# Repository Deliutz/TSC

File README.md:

# InkTime Smartwatch Project

Proiect hardware pentru realizarea unui smartwatch open-source low-cost, bazat pe microcontrollerul **Nordic nRF52840**, proiectat în **Autodesk Fusion 360 Electronics**.

---

# Diagrama bloc

```text
Baterie LiPo
    |
    v
+------------------+
|   BQ25180YBGR    |
| Charger / PMIC   |
+------------------+
    |
    v
+------------------+
|    RT6160AWSC    |
| Buck-Boost 3.3V  |
+------------------+
    |
    v
+------------------+
|    nRF52840      |
|   MCU + BLE      |
+------------------+
   |      |      |      |      |
   |      |      |      |      |
   |      |      |      |      +-------------------+
   |      |      |      |                          |
   |      |      |      v                          v
   |      |      |  +---------+              +-----------+
   |      |      |  | Buttons |              | TC2030    |
   |      |      |  | 3x GPIO |              | SWD Debug |
   |      |      |  +---------+              +-----------+
   |      |      |
   |      |      +-------------------+
   |      |                          |
   |      v                          v
   |  +-----------+            +------------+
   |  | DRV2605   |----------->| Vibra motor|
   |  | Haptic IC |            +------------+
   |  +-----------+
   |
   +---------------------+
   |                     |
   v                     v
+---------+         +-----------+
| BMA421  |         | MAX17048  |
| IMU     |         | Fuel Gauge|
+---------+         +-----------+
   ^                     ^
   |                     |
   +--------- I2C -------+

```

---

# Bill of Materials (BOM)

| Componenta | Cod | Rol | Interfata |
|---|---|---|---|
| NRF52840_QF | U1 | Microcontroller principal + BLE | SPI / I2C / GPIO |
| BQ25180YBGR | IC1 | Incarcare baterie LiPo / power management | Power / I2C |
| RT6160AWSC | IC9 | Convertor buck-boost 3.3V | Power |
| BMA421 | IC3 | Accelerometru / IMU | I2C |
| DRV2605YZFR | IC2 | Driver feedback haptic | I2C / GPIO |
| MAX17048G+T10 | U3 | Fuel gauge baterie | I2C |
| KH-TYPE-C-16P | J4 | Conector USB-C | USB |
| USBLC6-2SC6Y | D3 | Protectie ESD USB | USB |
| 503480-2400 | J2 | Conector display e-paper | SPI |
| 2450AT18B100E | ANT1 | Antena 2.4 GHz BLE | RF |
| TC2030-IDC | J1 | Conector debugging SWD | SWD |
| SW_UP / SW_ENT / SW_DN | SW_UP, SW_ENT, SW_DN | Input utilizator | GPIO |
| X1 | X1 | Cristal de mare frecventa pentru nRF52840 | Clock |
| X2 32.768kHz | X2 | Cristal RTC / low power clock | Clock |
| SI1308EDL-T1-GE3 | Q3 | MOSFET pentru comutare alimentare | Power / GPIO |
| Q1 | Q1 | MOSFET pentru power switching | Power |
| FTC252012SR47MBCA | L7 | Inductor pentru regulatorul de tensiune | Power |
| MBR0530 | D2, D4, D5 | Diode Schottky pentru protectie / redresare | Power |
| TP_* | TP_3.3V, TP_3V3, TP_BAT_GND, TP_GND, TP_ON, TP_OP, TP_RESET, TP_SCL, TP_SDA, TP_SWDCLK, TP_SWDIO, TP_SWO, TP_VBAT, TP_VREG | Test pads pentru validare si debugging | Test / Debug |

---

# Funcționalitate hardware
Designul este construit în jurul microcontrollerului **nRF52840**, responsabil de:
- comunicația Bluetooth Low Energy;
- citirea senzorilor;
- controlul display-ului e-paper;
- gestionarea butoanelor;
- controlul feedback-ului haptic;
- monitorizarea bateriei.

## Alimentare
- **BQ25180** gestionează încărcarea bateriei LiPo;
- **RT6160** generează tensiunea stabilă de **3.3V**;
- **MAX17048** monitorizează nivelul bateriei.

## Senzori și periferice
- **BMA423** este conectat prin **I2C**;
- display-ul e-paper este conectat prin conectorul FPC;
- **DRV2605** comandă motorul de vibrații;
- USB-C este folosit pentru alimentare și debugging.

---

# Utilizarea pinilor nRF52840
## Magistrală I2C
- SDA → IMU + Fuel Gauge
- SCL → IMU + Fuel Gauge

## SWD
- SWDIO
- SWDCLK
- SWO
- RESET

## GPIO
- Buton UP
- Buton ENTER
- Buton DOWN
- semnale control display
- semnal driver haptic

## SPI
- semnale rutate către conectorul display-ului e-paper

---

# Proces de proiectare

## 1. Schematic
În prima etapă am realizat schema electrică pornind de la modelul oferit pe OCW și folosind exclusiv biblioteca pusă la dispoziție.

Am implementat blocurile:
- LiPo Charger
- DC/DC
- IMU
- SWD
- E-Paper Driver
- Fuel Gauge
- Haptic Driver
- Buttons
- USB-C + ESD

În timpul realizării schemei:
- am modificat valorile componentelor pasive;
- am adăugat condensatoare de decuplare;
- am etichetat semnalele importante;
- am separat schematicul pe blocuri funcționale.

---

## 2. PCB Design
PCB-ul a fost realizat pe baza dimensiunilor mecanice recomandate.

Etapele principale:
- placement TOP pentru componentele critice;
- amplasarea componentelor pasive lângă pinii de alimentare;
- rutare pe mai multe straturi;
- plane dedicate de GND;
- păstrarea zonei antenei liberă;
- alinierea USB-C și a butoanelor cu carcasa.

La final am rulat DRC și am corectat erorile principale.

---

## 3. Model 3D
Modelul 3D include:
- PCB
- baterie
- display
- carcasă

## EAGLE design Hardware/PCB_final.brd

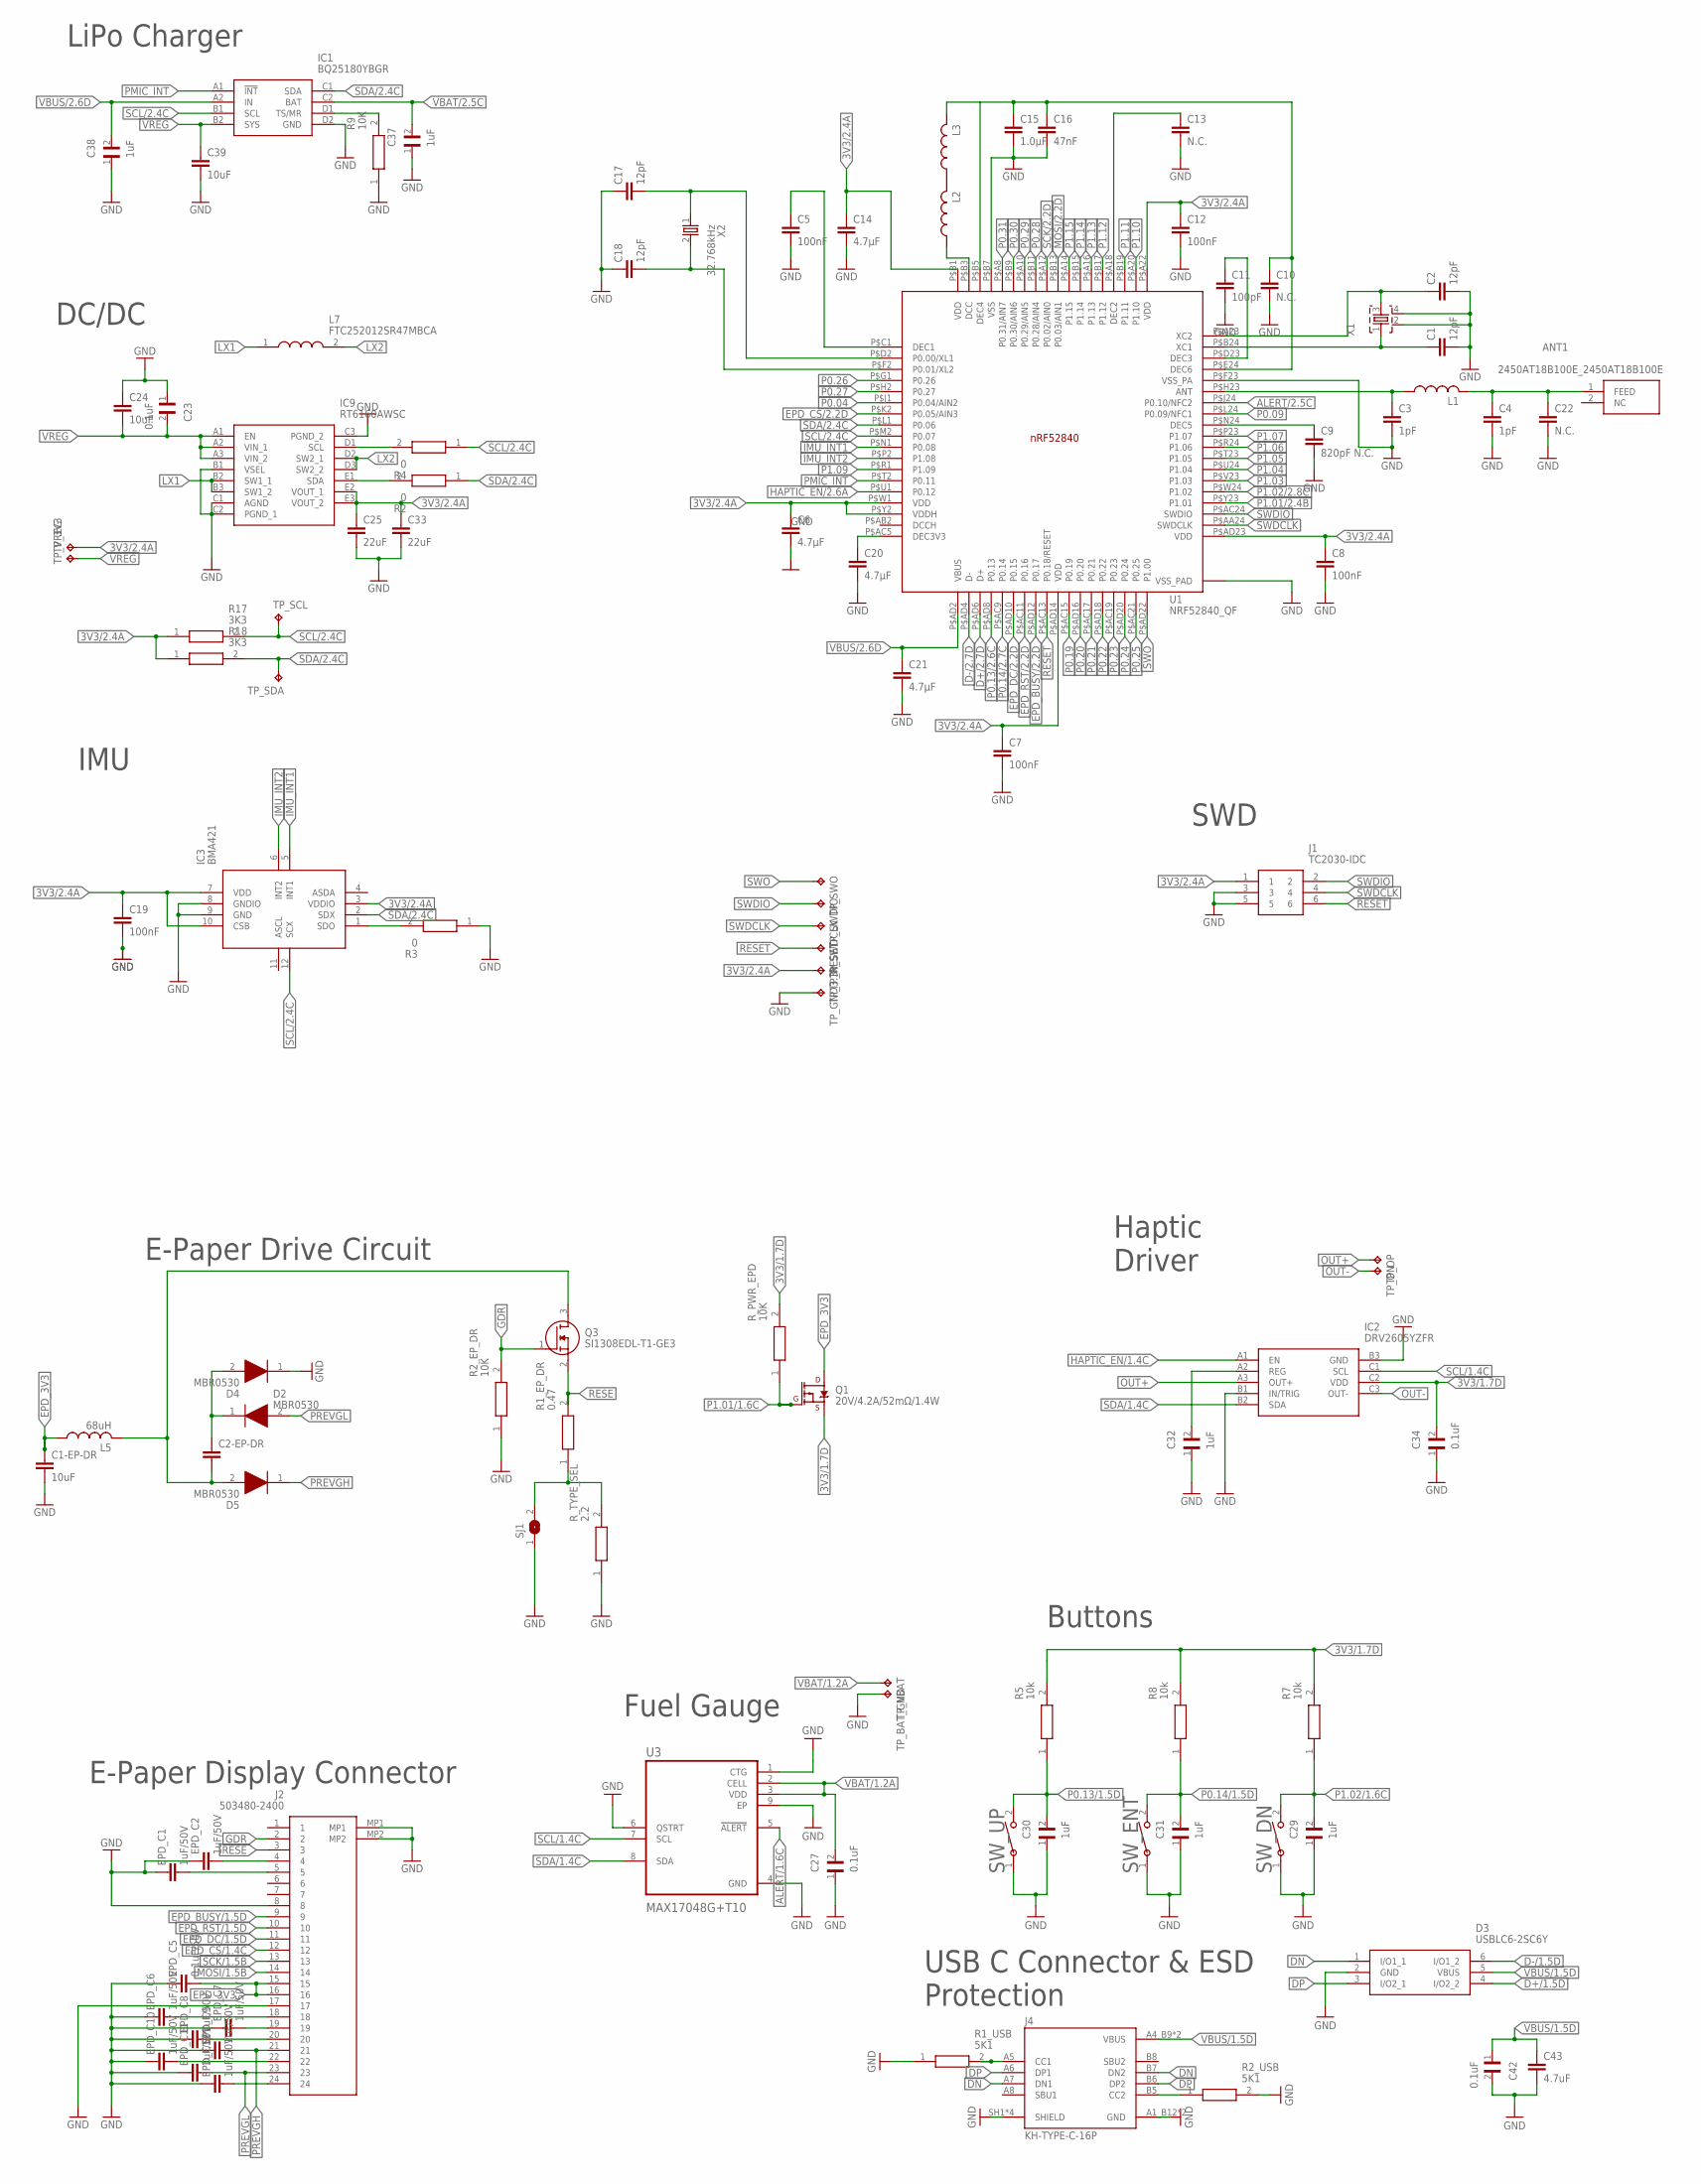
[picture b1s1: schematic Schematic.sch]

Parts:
ANT1: 2450AT18B100E_2450AT18B100E; 2450AT18B100E_ANTC3216X140N
C1, C2, C17, C18: 12pF; NORDIC_NRF_3_RESC0201_L
C1-EP-DR, C24, C39: 10uF; NORDIC_NRF_3_RESC0201_L
C2-EP-DR: NORDIC_NRF_3_CAPACITOR_0201_L; NORDIC_NRF_3_RESC0201_L
C3, C4: 1pF; NORDIC_NRF_3_RESC0201_L
C5, C7, C8, C12, C19: 100nF; NORDIC_NRF_3_RESC0201_L
C6: 4.7µF; NORDIC_NRF_3_RESC0201_L
C9: 820pF N.C.; NORDIC_NRF_3_RESC0201_L
C10, C13, C22: N.C.; NORDIC_NRF_3_RESC0201_L
C11: 100pF; NORDIC_NRF_3_RESC0201_L
C14, C20, C21: 4.7µF; ESP32_C6_LIBRARY_1_ESP32_WROVER_EAGLE-LTSPICE_C0402
C15: 1.0µF; NORDIC_NRF_3_RESC0201_L
C16: 47nF; NORDIC_NRF_3_RESC0201_L
C23, C34: 0.1uF; GRM011R60J152KE01L_2_CAPC0201X13N
C25, C33: 22uF; NORDIC_NRF_3_RESC0201_L
C27, C42: 0.1uF; GRM011R60J152KE01L_1_0201
C29, C30, C31: 1uF; GRM011R60J152KE01L_1_0201
C32, C37, C38: 1uF; GRM011R60J152KE01L_2_CAPC0201X13N
C43: 4.7uF; NORDIC_NRF_3_RESC0201_L
D2, D4, D5: MBR0530; ESP32_C6_LIBRARY_5_SOD3716X135N
D3: USBLC6-2SC6Y; ESP32_C6_LIBRARY_3_SOT95P280X145-6N
EPD_C1, EPD_C2, EPD_C6, EPD_C7, EPD_C8, EPD_C9, EPD_C10, EPD_C11, EPD_C12: 1uF/50V; PERFECT_0402_0402
EPD_C5: 0.1uF/50V; PERFECT_0402_0402
IC1: BQ25180YBGR; BQ25180YBGR_BGA8C40P2X4_100X155X50
IC2: DRV2605YZFR; DRV2605YZFR_BGA9C50P3X3_144X144X62
IC3: BMA421; BMA423_BMA423
IC9: RT6160AWSC; RT6160AWSC_BGA15C40P3X5_140X230X60
J1: TC2030-IDC; TC2030-IDC_TC2030IDC
J2: 503480-2400; 503480-2400_5034802400
J4: KH-TYPE-C-16P; KH-TYPE-C-16P_KINGHELM_KH-TYPE-C-16P
L1, L2, L3: NORDIC_NRF_2_INDUCTOR_0402_L; NORDIC_NRF_2_RESC0402_L
L5: 68uH; NORDIC_NRF_2_RESC0402_L
L7: FTC252012SR47MBCA; MLP2016SR47MT0S1_INDC2016X100N
Q1: 20V/4.2A/52mΩ/1.4W; ESP32_C6_LIBRARY_4_ESP32_C6_LIBRARY_4_ESP32_C6_LIBRARY_4_ES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
Q3: SI1308EDL-T1-GE3; ESP32_C6_LIBRARY_6_SOT65P210X110-3N
R1_EP_DR: 0.47; ERA-1AEB3401C_0201
R1_USB, R2_USB: 5K1; CPF0201D7K68C1_0201
R2, R4: 0; ERA-1AEB3401C_0201
R2_EP_DR, R9: 10K; ERA-1AEB3401C_0201
R3: 0; CPF0201D7K68C1_0201
R5, R7, R8: 10k; CPF0201D7K68C1_0201
R17, R18: 3K3; ERA-1AEB3401C_0201
R_PWR_EPD: 10K; ERA-1AEB3401C_0201
R_TYPE_SEL: 2.2; ERA-1AEB3401C_0201
SJ1: ESP32_C6_LIBRARY_7_JUMPER_SJ
SW_DN: 2025-10-22_07-23-44_LIBRARY_EVP-AKE31ASW_EVP-AKE3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; 2025-10-22_07-23-44_LIBRARY_SW_EVP-AKE31A_PAN
SW_ENT: 2025-10-22_07-23-44_LIBRARY_EVP-AKE31ASW_EVP-AKE3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; 2025-10-22_07-23-44_LIBRARY_SW_EVP-AKE31A_PAN
SW_UP: 2025-10-22_07-23-44_LIBRARY_EVP-AKE31ASW_EVP-AKE3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; 2025-10-22_07-23-44_LIBRARY_SW_EVP-AKE31A_PAN
TP_3.3V, TP_3V3: HECTOR_WATCH_1_TPTP20R; HECTOR_WATCH_1_TP20R
TP_BAT_GND: HECTOR_WATCH_1_TPTP20R; HECTOR_WATCH_1_TP20R
TP_GND: HECTOR_WATCH_1_TPTP20R; HECTOR_WATCH_1_TP20R
TP_ON: HECTOR_WATCH_1_TPTP20R; HECTOR_WATCH_1_TP20R
TP_OP: HECTOR_WATCH_1_TPTP20R; HECTOR_WATCH_1_TP20R
TP_RESET: HECTOR_WATCH_1_TPTP20R; HECTOR_WATCH_1_TP20R
TP_SCL: HECTOR_WATCH_1_TPTP20R; HECTOR_WATCH_1_TP20R
TP_SDA: HECTOR_WATCH_1_TPTP20R; HECTOR_WATCH_1_TP20R
TP_SWDCLK: HECTOR_WATCH_1_TPTP20R; HECTOR_WATCH_1_TP20R
TP_SWDIO: HECTOR_WATCH_1_TPTP20R; HECTOR_WATCH_1_TP20R
TP_SWO: HECTOR_WATCH_1_TPTP20R; HECTOR_WATCH_1_TP20R
TP_VBAT: HECTOR_WATCH_1_TPTP20R; HECTOR_WATCH_1_TP20R
TP_VREG: HECTOR_WATCH_1_TPTP20R; HECTOR_WATCH_1_TP20R
U1: NRF52840_QF; NORDIC_NRF_4_AQFN50P700X700X85_HS-74N
U3: MAX17048G+T10; ESP32_C6_LIBRARY_SON50P200X200X80-9N
X1: NORDIC_NRF_XTAL_32MHZ; NORDIC_NRF_BT-XTAL_2016_N
X2: 32.768kHz; NORDIC_NRF_1_XTAL_3215_N

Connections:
3V3/1.7D: C34.2, IC2.C2 (VDD), Q1.2 (S), R5.2, R7.2, R8.2, R_PWR_EPD.2
3V3/2.4A: C6.1, C7.1, C8.1, C12.1, C14.1, C19.1, C25.1, C33.1, IC3.3 (VDDIO), IC3.7 (VDD), IC3.10 (CSB), IC9.E2 (VOUT_1), IC9.E3 (VOUT_2), J1.1, R17.1, R18.1, TP_3.3V.TP, TP_3V3.TP, U1.P$A22 (VDD), U1.P$AD14 (VDD), U1.P$AD23 (VDD), U1.P$B1 (VDD), U1.P$W1 (VDD), U1.P$Y2 (VDDH)
ALERT/1.6C: U3.5 (!ALERT)
ALERT/2.5C: U1.P$J24 (P0.10/NFC2)
D+/1.5D: D3.4 (I/O2_2)
D+/2.7D: U1.P$AD6 (D+)
D-/1.5D: D3.6 (I/O1_2)
D-/2.7D: U1.P$AD4 (D-)
DN: D3.1 (I/O1_1), J4.A7 (DN1), J4.B7 (DN2)
DP: D3.3 (I/O2_1), J4.A6 (DP1), J4.B6 (DP2)
EPD_3V3: C1-EP-DR.1, EPD_C5.2, J2.15, J2.16, L5.1, Q1.3 (D)
EPD_BUSY/1.5D: J2.9
EPD_BUSY/2.2D: U1.P$AD12 (P0.17)
EPD_CS/1.4C: J2.12
EPD_CS/2.2D: U1.P$K2 (P0.05/AIN3)
EPD_DC/1.5D: J2.11
EPD_DC/2.2D: U1.P$AD10 (P0.15)
EPD_RST/1.5D: J2.10
EPD_RST/2.2D: U1.P$AC11 (P0.16)
GDR: J2.2, Q3.1 (G), R2_EP_DR.2
GND: C1.2, C1-EP-DR.2, C2.2, C3.2, C4.2, C5.2, C6.2, C7.2, C8.2, C9.2, C10.2, C11.2, C12.2, C13.2, C14.2, C15.2, C16.2, C17.1, C18.1, C19.2, C20.2, C21.2, C22.2, C23.1, C24.1, C25.2, C27.1, C29.1, C30.1, C31.1, C32.1, C33.2, C34.1, C37.1, C38.1, C39.2, C42.2, C43.2, D3.2 (GND), D4.1 (K), EPD_C1.1, EPD_C2.1, EPD_C5.1, EPD_C6.1, EPD_C7.1, EPD_C8.1, EPD_C9.1, EPD_C10.1, EPD_C11.1, EPD_C12.1, IC1.D2 (GND), IC2.B1 (IN/TRIG), IC2.B3 (GND), IC3.8 (GNDIO), IC3.9 (GND), IC9.B1 (VSEL), IC9.C1 (AGND), IC9.C2 (PGND_1), IC9.C3 (PGND_2), J1.3, J1.5, J2.8, J2.17, J2.MP1, J2.MP2, J4.A1_B12 (GND), J4.A12_B1 (GND), J4.SH1 (SHIELD), J4.SH2 (SHIELD), J4.SH3 (SHIELD), J4.SH4 (SHIELD), R1_USB.1, R2_EP_DR.1, R2_USB.2, R3.1, R9.1, R_TYPE_SEL.1, SJ1.1, SW_DN.1, SW_ENT.1, SW_UP.1, TP_BAT_GND.TP, TP_GND.TP, U1.P$74 (VSS_PAD), U1.P$75 (VSS_PAD), U1.P$76 (VSS_PAD), U1.P$77 (VSS_PAD), U1.P$78 (VSS_PAD), U1.P$79 (VSS_PAD), U1.P$80 (VSS_PAD), U1.P$81 (VSS_PAD), U1.P$82 (VSS_PAD), U1.P$83 (VSS_PAD), U1.P$84 (VSS_PAD), U1.P$85 (VSS_PAD), U1.P$86 (VSS_PAD), U1.P$87 (VSS_PAD), U1.P$88 (VSS_PAD), U1.P$89 (VSS_PAD), U1.P$90 (VSS_PAD), U1.P$B7 (VSS), U1.P$F23 (VSS_PA), U3.1 (CTG), U3.4 (GND), U3.6 (QSTRT), U3.9 (EP), X1.2, X1.4
HAPTIC_EN/1.4C: IC2.A1 (EN)
HAPTIC_EN/2.6A: U1.P$U1 (P0.12)
IMU_INT1: IC3.5 (INT1), U1.P$N1 (P0.08)
IMU_INT2: IC3.6 (INT2), U1.P$P2 (P1.08)
LX1: IC9.B2 (SW1_1), IC9.B3 (SW1_2), L7.1
LX2: IC9.D2 (SW2_1), IC9.D3 (SW2_2), L7.2
MOSI/1.5B: J2.14
MOSI/2.2D: U1.P$B13 (P0.03/AIN1)
unnamed: IC1.D1 (TS/MR), R9.2
unnamed: L2.2, L3.1
unnamed: C10.1, C15.1, C16.1, L3.2, U1.P$E24 (DEC6)
unnamed: ANT1.1 (FEED), C4.1, C22.1, L1.2
unnamed: IC9.D1 (SCL), R4.2
unnamed: C2-EP-DR.2, D5.2 (A), L5.2, Q3.3 (D)
unnamed: IC9.E1 (SDA), R2.2
unnamed: C2-EP-DR.1, D2.1 (K), D4.2 (A)
unnamed: IC3.1 (SDO), R3.2
unnamed: EPD_C2.2, J2.4
unnamed: C32.2, IC2.A2 (REG)
unnamed: EPD_C1.2, J2.5
unnamed: C20.1, U1.P$AC5 (DEC3V3)
unnamed: C5.1, U1.P$C1 (DEC1)
unnamed: C17.2, U1.P$D2 (P0.00/XL1), X2.1
unnamed: C18.2, U1.P$F2 (P0.01/XL2), X2.2
unnamed: R1_EP_DR.1, R_TYPE_SEL.2, SJ1.2
unnamed: L2.1, U1.P$B3 (DCC)
unnamed: J4.A5 (CC1), R1_USB.2
unnamed: C3.1, L1.1, U1.P$H23 (ANT)
unnamed: C9.1, U1.P$N24 (DEC5)
unnamed: C1.1, U1.P$B24 (XC1), X1.1
unnamed: C2.1, U1.P$A23 (XC2), X1.3
unnamed: C11.1, U1.P$D23 (DEC3)
unnamed: C13.1, U1.P$A18 (DEC2)
unnamed: EPD_C6.2, J2.18
unnamed: EPD_C7.2, J2.19
unnamed: EPD_C8.2, J2.20
unnamed: J4.B5 (CC2), R2_USB.1
unnamed: EPD_C10.2, J2.22
unnamed: EPD_C12.2, J2.24
OUT+: IC2.A3 (OUT+), TP_OP.TP
OUT-: IC2.C3 (OUT-), TP_ON.TP
P0.04: U1.P$J1 (P0.04/AIN2)
P0.09: U1.P$L24 (P0.09/NFC1)
P0.13/1.5D: C30.2, R5.1, SW_UP.2
P0.13/2.6C: U1.P$AD8 (P0.13)
P0.14/1.5D: C31.2, R8.1, SW_ENT.2
P0.14/2.7C: U1.P$AC9 (P0.14)
P0.19: U1.P$AC15 (P0.19)
P0.20: U1.P$AD16 (P0.20)
P0.21: U1.P$AC17 (P0.21)
P0.22: U1.P$AD18 (P0.22)
P0.23: U1.P$AC19 (P0.23)
P0.24: U1.P$AD20 (P0.24)
P0.25: U1.P$AC21 (P0.25)
P0.26: U1.P$G1 (P0.26)
P0.27: U1.P$H2 (P0.27)
P0.28: U1.P$B11 (P0.28/AIN4)
P0.29: U1.P$A10 (P0.29/AIN5)
P0.30: U1.P$B9 (P0.30/AIN6)
P0.31: U1.P$A8 (P0.31/AIN7)
P1.01/1.6C: Q1.1 (G), R_PWR_EPD.1
P1.01/2.4B: U1.P$Y23 (P1.01)
P1.02/1.6C: C29.2, R7.1, SW_DN.2
P1.02/2.8C: U1.P$W24 (P1.02)
P1.03: U1.P$V23 (P1.03)
P1.04: U1.P$U24 (P1.04)
P1.05: U1.P$T23 (P1.05)
P1.06: U1.P$R24 (P1.06)
P1.07: U1.P$P23 (P1.07)
P1.09: U1.P$R1 (P1.09)
P1.10: U1.P$A20 (P1.10)
P1.11: U1.P$B19 (P1.11)
P1.12: U1.P$B17 (P1.12)
P1.13: U1.P$A16 (P1.13)
P1.14: U1.P$B15 (P1.14)
P1.15: U1.P$A14 (P1.15)
PMIC_INT: IC1.A1 (!INT), U1.P$T2 (P0.11)
PREVGH: D5.1 (K), EPD_C9.2, J2.21
PREVGL: D2.2 (A), EPD_C11.2, J2.23
RESE: J2.3, Q3.2 (S), R1_EP_DR.2
RESET: J1.6, TP_RESET.TP, U1.P$AC13 (P0.18/RESET)
SCK/1.5B: J2.13
SCK/2.2D: U1.P$A12 (P0.02/AIN0)
SCL/1.4C: IC2.C1 (SCL), U3.7 (SCL)
SCL/2.4C: IC1.B1 (SCL), IC3.12 (SCX), R4.1, R17.2, TP_SCL.TP, U1.P$M2 (P0.07)
SDA/1.4C: IC2.B2 (SDA), U3.8 (SDA)
SDA/2.4C: IC1.C1 (SDA), IC3.2 (SDX), R2.1, R18.2, TP_SDA.TP, U1.P$L1 (P0.06)
SWDCLK: J1.4, TP_SWDCLK.TP, U1.P$AA24 (SWDCLK)
SWDIO: J1.2, TP_SWDIO.TP, U1.P$AC24 (SWDIO)
SWO: TP_SWO.TP, U1.P$AD22 (P1.00)
VBAT/1.2A: C27.2, TP_VBAT.TP, U3.2 (CELL), U3.3 (VDD)
VBAT/2.5C: C37.2, IC1.C2 (BAT)
VBUS/1.5D: C42.1, C43.1, D3.5 (VBUS), J4.A4_B9 (VBUS), J4.A9_B4 (VBUS)
VBUS/2.6D: C21.1, C38.2, IC1.A2 (IN), U1.P$AD2 (VBUS)
VREG: C23.2, C24.2, C39.1, IC1.B2 (SYS), IC9.A1 (EN), IC9.A2 (VIN_1), IC9.A3 (VIN_2), TP_VREG.TP

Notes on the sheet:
LiPo Charger
DC/DC
IMU
SWD
E-Paper Drive Circuit
Haptic Driver
E-Paper Display Connector
Fuel Gauge
Buttons
USB C Connector & ESD Protection

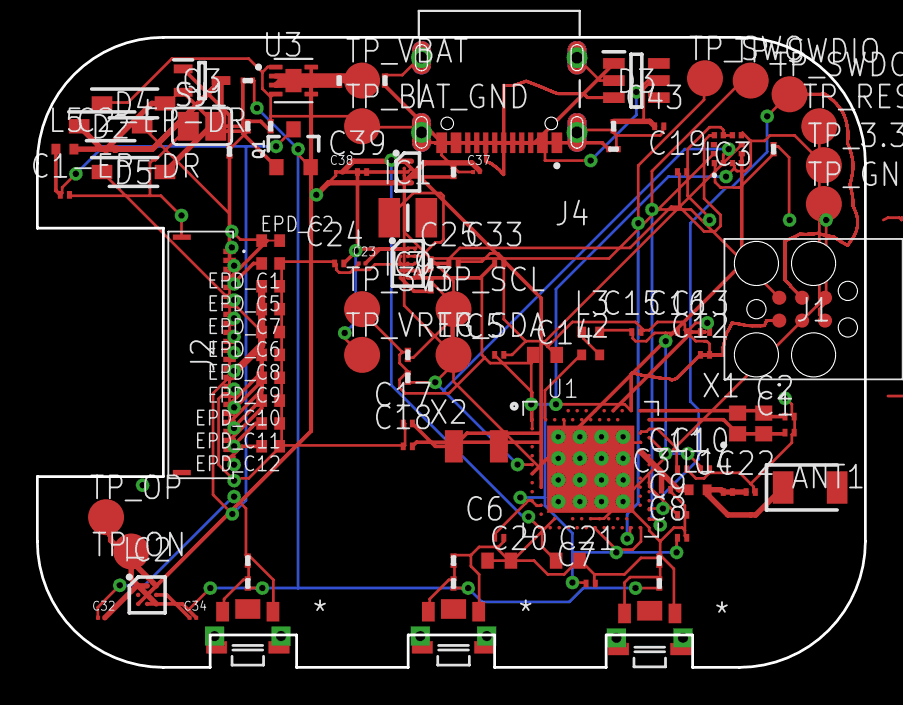
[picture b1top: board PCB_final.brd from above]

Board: 4 copper layers, 46.0 x 35.0 mm, 105 parts (0 on the bottom side), 65 nets.

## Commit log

2026-04-10 Create README with project overview and design details
    Added detailed documentation for schematic, PCB design, and 3D model of the smartwatch project.
2026-04-18 Create Mechanical
2026-04-18 README.md
    Updated block diagram and BOM for clarity and accuracy.

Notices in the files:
parts and their libraries:
COPYRIGHT: Copyright (C) 2025 Ultra Librarian. All rights reserved.
